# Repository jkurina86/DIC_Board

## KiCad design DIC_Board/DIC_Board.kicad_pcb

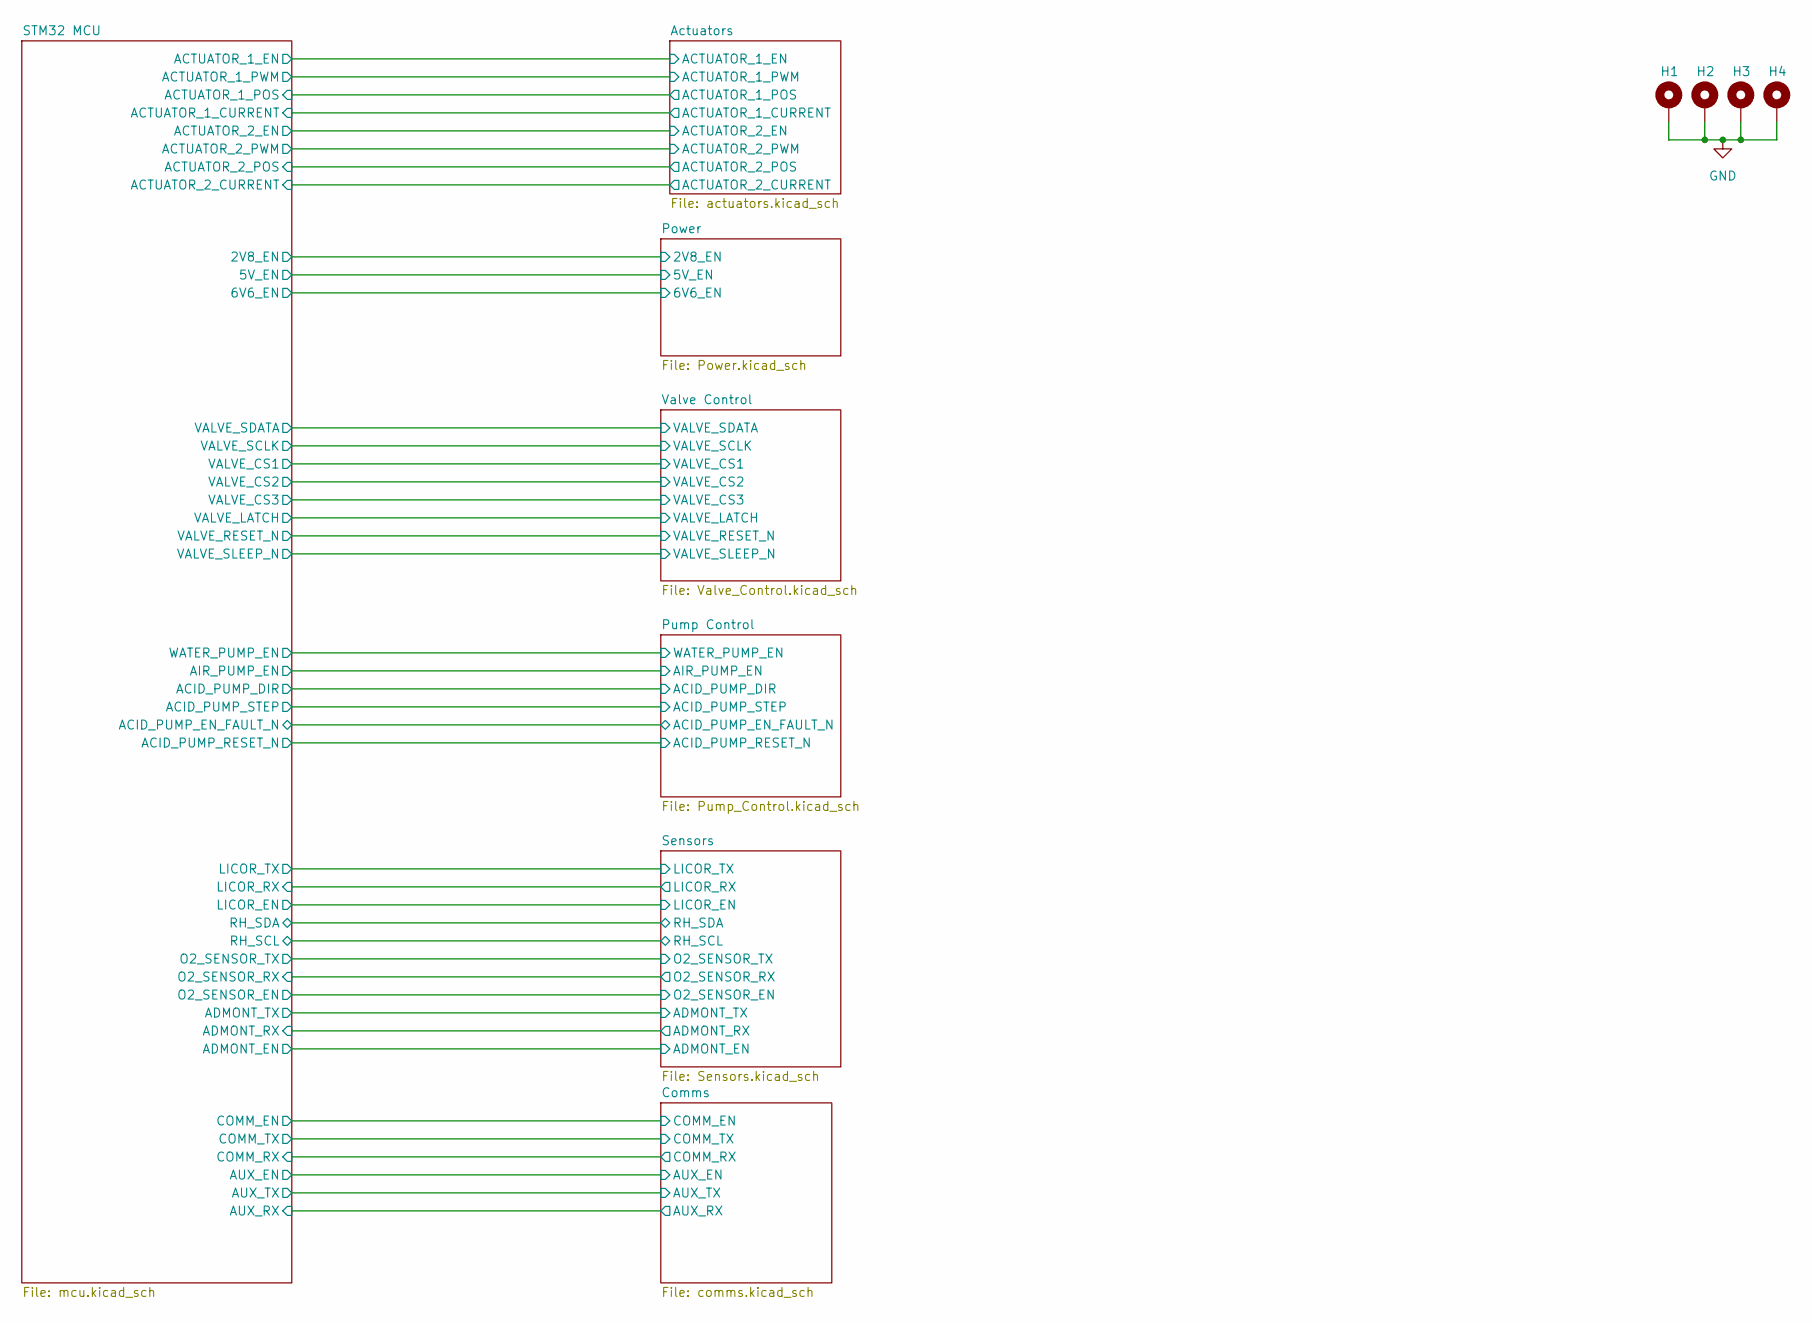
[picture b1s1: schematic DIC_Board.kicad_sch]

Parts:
H1, H2, H3, H4: MountingHole_2.5mm_Pad

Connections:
GND: H1.1 (1_1), H2.1 (1_1), H3.1 (1_1), H4.1 (1_1); also elsewhere on the board

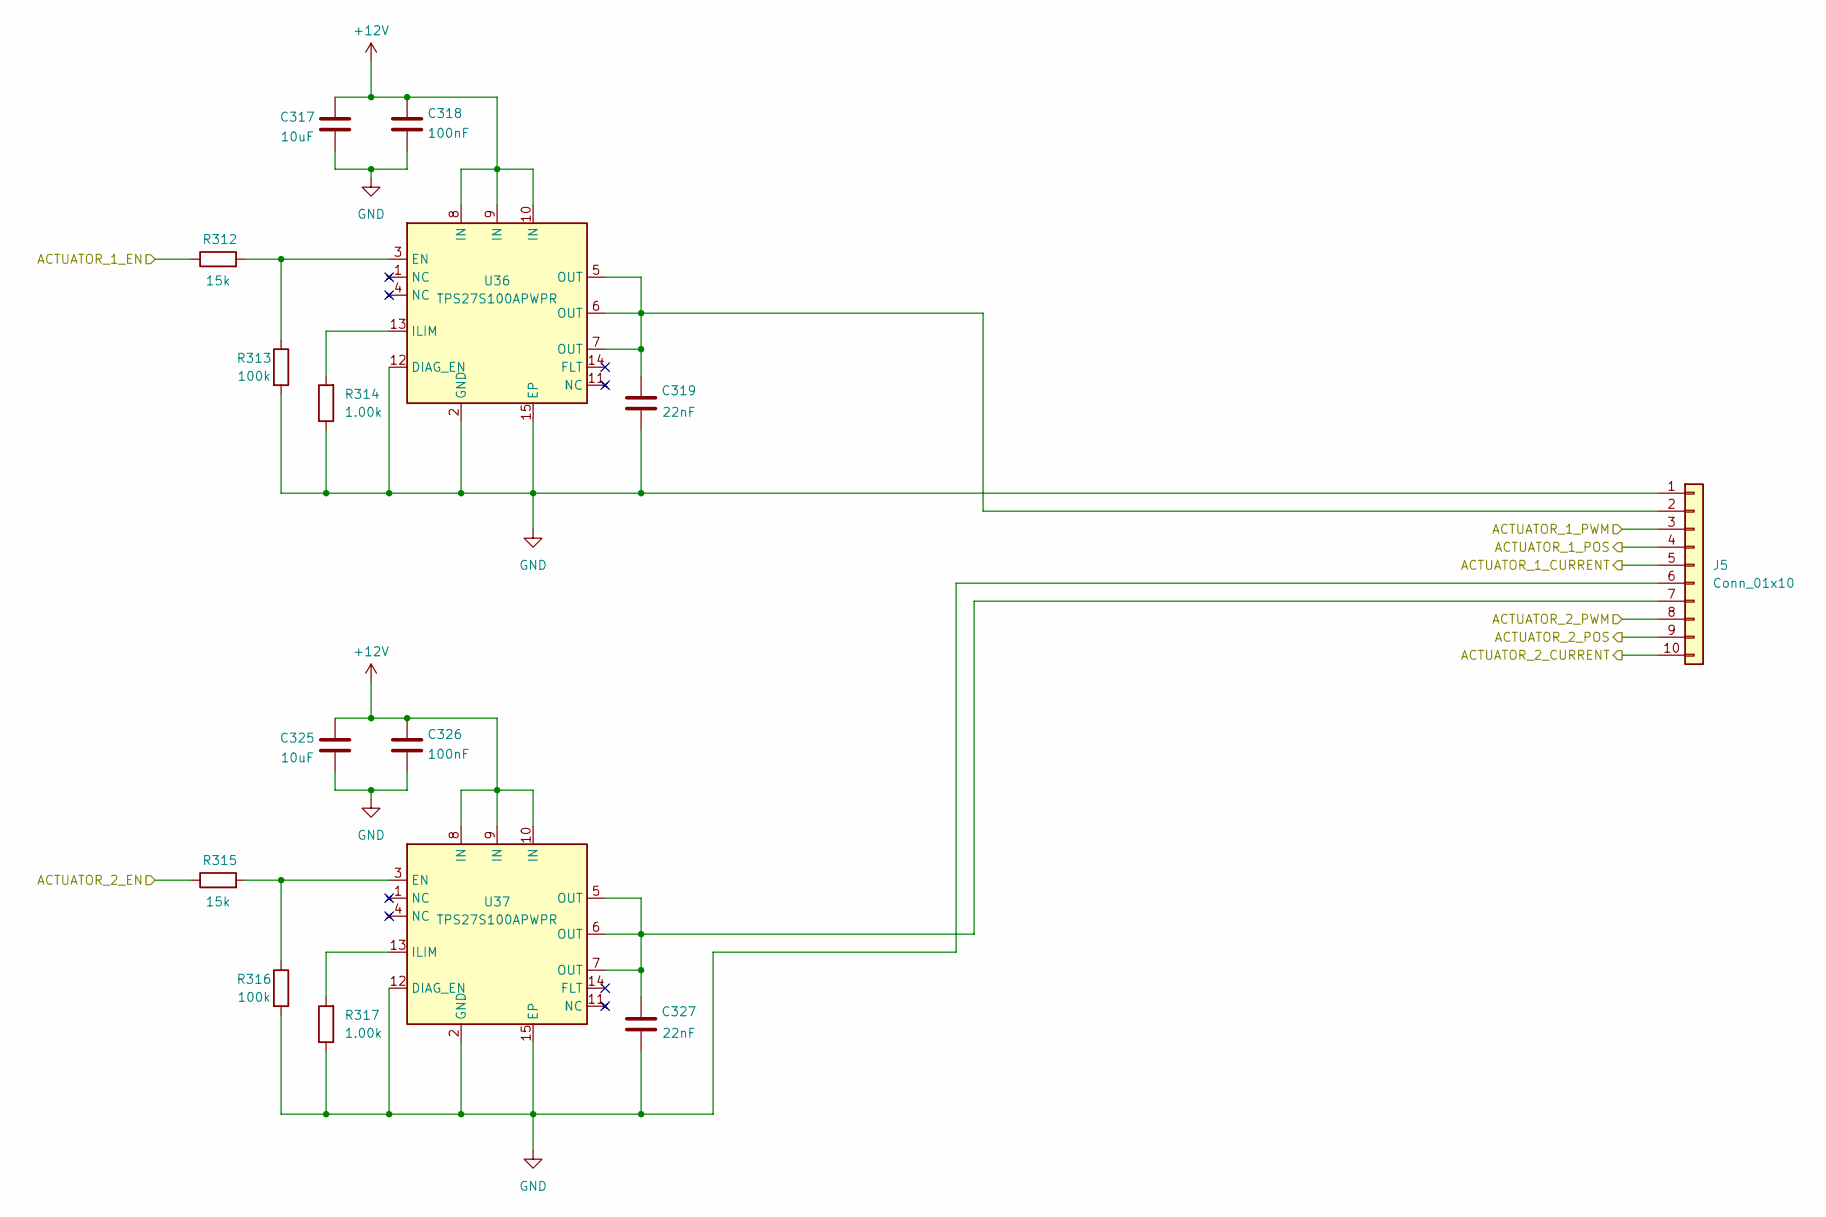
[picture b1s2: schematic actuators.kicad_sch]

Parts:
C317, C325: 10uF; C_1206_3216Metric; MPN CGA5L1X7R1H106K160AC
C318, C326: 100nF; C_0402_1005Metric; MPN GRM155R71H104ME14D
C319, C327: 22nF; C_0402_1005Metric; MPN GRM155R71H223KA12D
J5: Conn_01x10; Molex_Micro-Fit_3.0_43045-1000_2x05_P3.00mm_Horizontal; MPN 0430451000
R312, R315: 15k; R_0402_1005Metric; MPN CRCW040215K0FKED
R313, R316: 100k; R_0402_1005Metric; MPN CRCW0402100KFKED
R314, R317: 1.00k; R_0402_1005Metric; MPN CRCW04021K00FKED
U36, U37: TPS27S100APWPR; TPS27S100_Thermal_Drill0p3; MPN TPS27S100APWPR; DigiKey 296-49002-1-ND

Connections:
+12V: C317.1, C318.1, C325.1, C326.1, U36.8 (IN), U36.9 (IN), U36.10 (IN), U37.8 (IN), U37.9 (IN), U37.10 (IN); also elsewhere on the board
/Actuators/ACTUATOR_1_CURRENT: J5.5; also elsewhere on the board
/Actuators/ACTUATOR_1_EN: R312.1; also elsewhere on the board
/Actuators/ACTUATOR_1_POS: J5.4; also elsewhere on the board
/Actuators/ACTUATOR_1_PWM: J5.3; also elsewhere on the board
/Actuators/ACTUATOR_2_CURRENT: J5.10; also elsewhere on the board
/Actuators/ACTUATOR_2_EN: R315.1; also elsewhere on the board
/Actuators/ACTUATOR_2_POS: J5.9; also elsewhere on the board
/Actuators/ACTUATOR_2_PWM: J5.8; also elsewhere on the board
GND: C317.2, C318.2, C319.2, C325.2, C326.2, C327.2, J5.1, J5.6, R313.2, R314.1, R316.2, R317.1, U36.2 (GND), U36.12 (DIAG_EN), U36.15 (EP), U37.2 (GND), U37.12 (DIAG_EN), U37.15 (EP); also elsewhere on the board
unnamed: C319.1, J5.2, U36.5 (OUT), U36.6 (OUT), U36.7 (OUT)
unnamed: C327.1, J5.7, U37.5 (OUT), U37.6 (OUT), U37.7 (OUT)
unnamed: R312.2, R313.1, U36.3 (EN)
unnamed: R314.2, U36.13 (ILIM)
unnamed: R315.2, R316.1, U37.3 (EN)
unnamed: R317.2, U37.13 (ILIM)

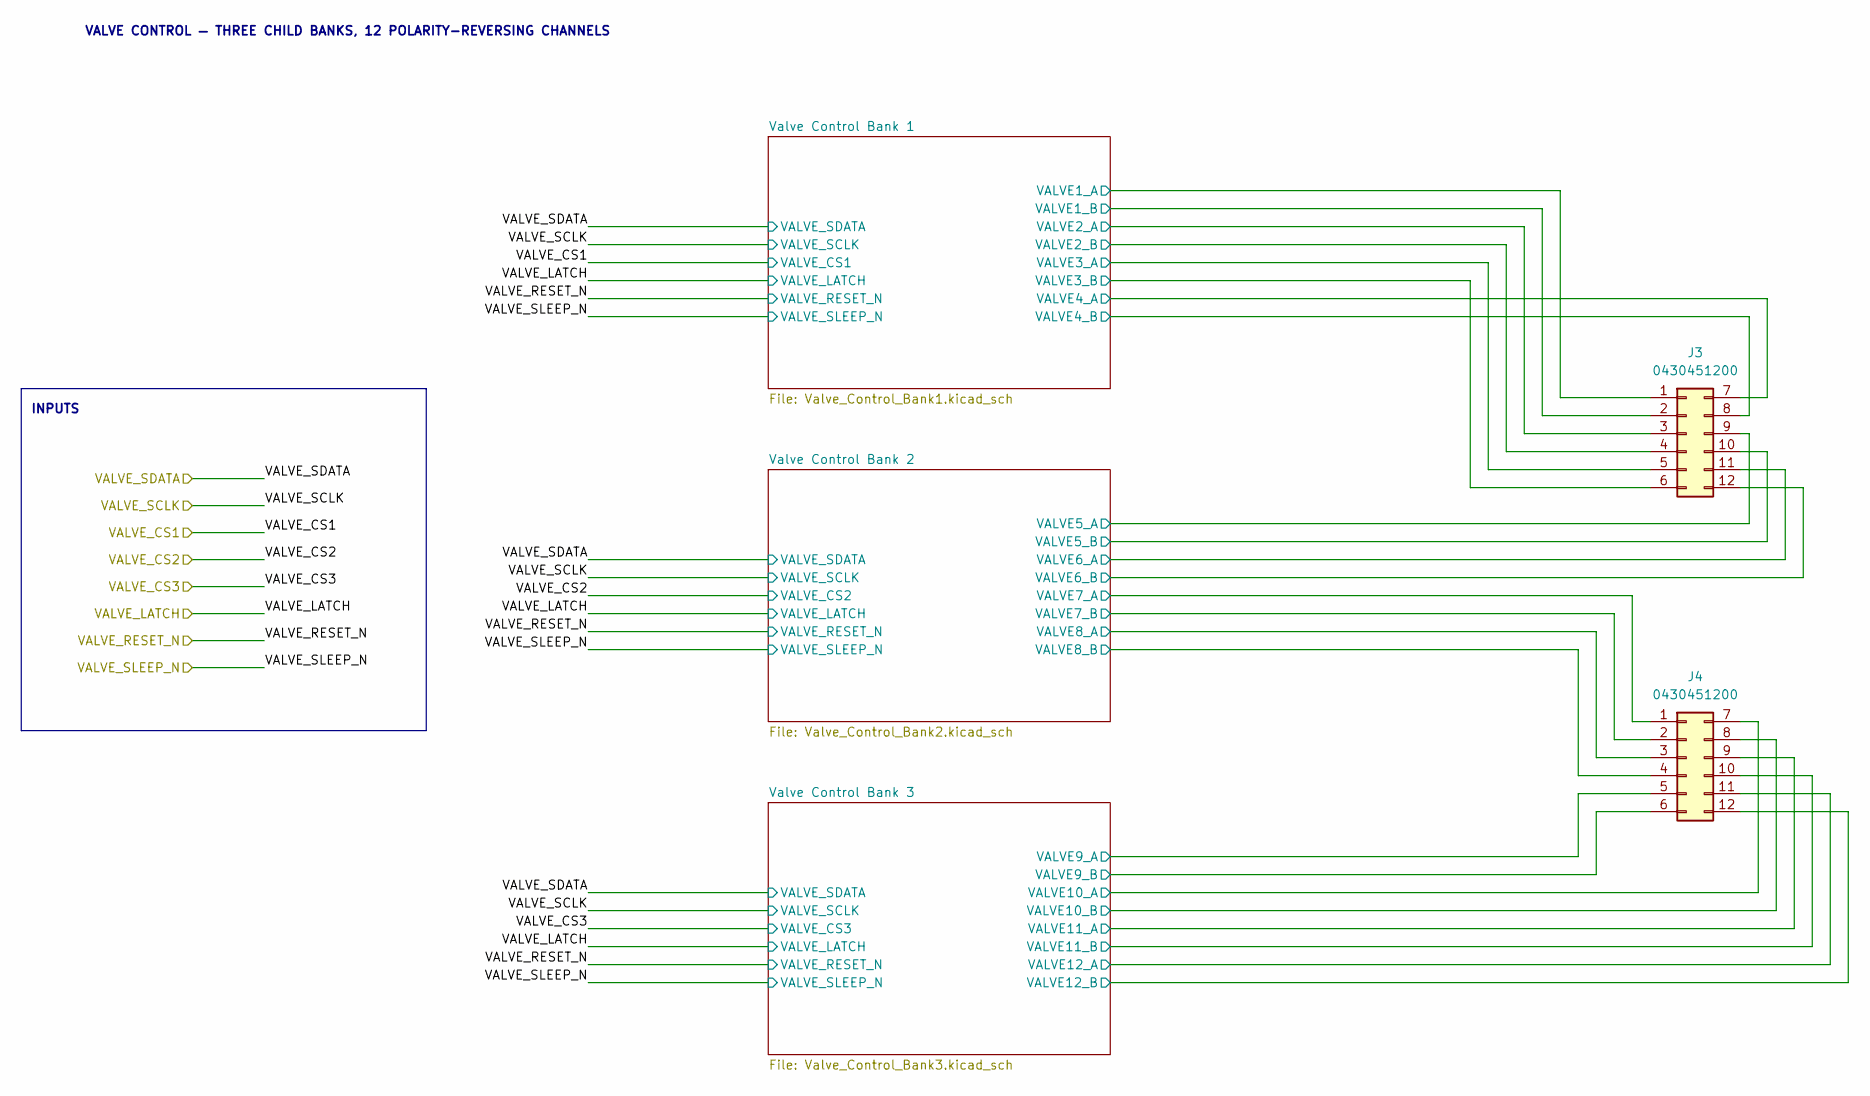
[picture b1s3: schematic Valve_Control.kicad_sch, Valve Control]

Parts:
J3, J4: 0430451200; Molex_Micro-Fit_3.0_43045-1200_2x06_P3.00mm_Horizontal; MPN 0430451200; DigiKey WM1818-ND

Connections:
/Valve Control/Valve Control Bank 1/VALVE1_A: J3.1; also elsewhere on the board
/Valve Control/Valve Control Bank 1/VALVE1_B: J3.2; also elsewhere on the board
/Valve Control/Valve Control Bank 1/VALVE2_A: J3.3; also elsewhere on the board
/Valve Control/Valve Control Bank 1/VALVE2_B: J3.4; also elsewhere on the board
/Valve Control/Valve Control Bank 1/VALVE3_A: J3.5; also elsewhere on the board
/Valve Control/Valve Control Bank 1/VALVE3_B: J3.6; also elsewhere on the board
/Valve Control/Valve Control Bank 1/VALVE4_A: J3.7; also elsewhere on the board
/Valve Control/Valve Control Bank 1/VALVE4_B: J3.8; also elsewhere on the board
/Valve Control/Valve Control Bank 2/VALVE5_A: J3.9; also elsewhere on the board
/Valve Control/Valve Control Bank 2/VALVE5_B: J3.10; also elsewhere on the board
/Valve Control/Valve Control Bank 2/VALVE6_A: J3.11; also elsewhere on the board
/Valve Control/Valve Control Bank 2/VALVE6_B: J3.12; also elsewhere on the board
/Valve Control/Valve Control Bank 2/VALVE7_A: J4.1; also elsewhere on the board
/Valve Control/Valve Control Bank 2/VALVE7_B: J4.2; also elsewhere on the board
/Valve Control/Valve Control Bank 2/VALVE8_A: J4.3; also elsewhere on the board
/Valve Control/Valve Control Bank 2/VALVE8_B: J4.4; also elsewhere on the board
/Valve Control/Valve Control Bank 3/VALVE9_A: J4.5; also elsewhere on the board
/Valve Control/Valve Control Bank 3/VALVE9_B: J4.6; also elsewhere on the board
/Valve Control/Valve Control Bank 3/VALVE10_A: J4.7; also elsewhere on the board
/Valve Control/Valve Control Bank 3/VALVE10_B: J4.8; also elsewhere on the board
/Valve Control/Valve Control Bank 3/VALVE11_A: J4.9; also elsewhere on the board
/Valve Control/Valve Control Bank 3/VALVE11_B: J4.10; also elsewhere on the board
/Valve Control/Valve Control Bank 3/VALVE12_A: J4.11; also elsewhere on the board
/Valve Control/Valve Control Bank 3/VALVE12_B: J4.12; also elsewhere on the board

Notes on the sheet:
INPUTS
VALVE CONTROL — THREE CHILD BANKS, 12 POLARITY-REVERSING CHANNELS

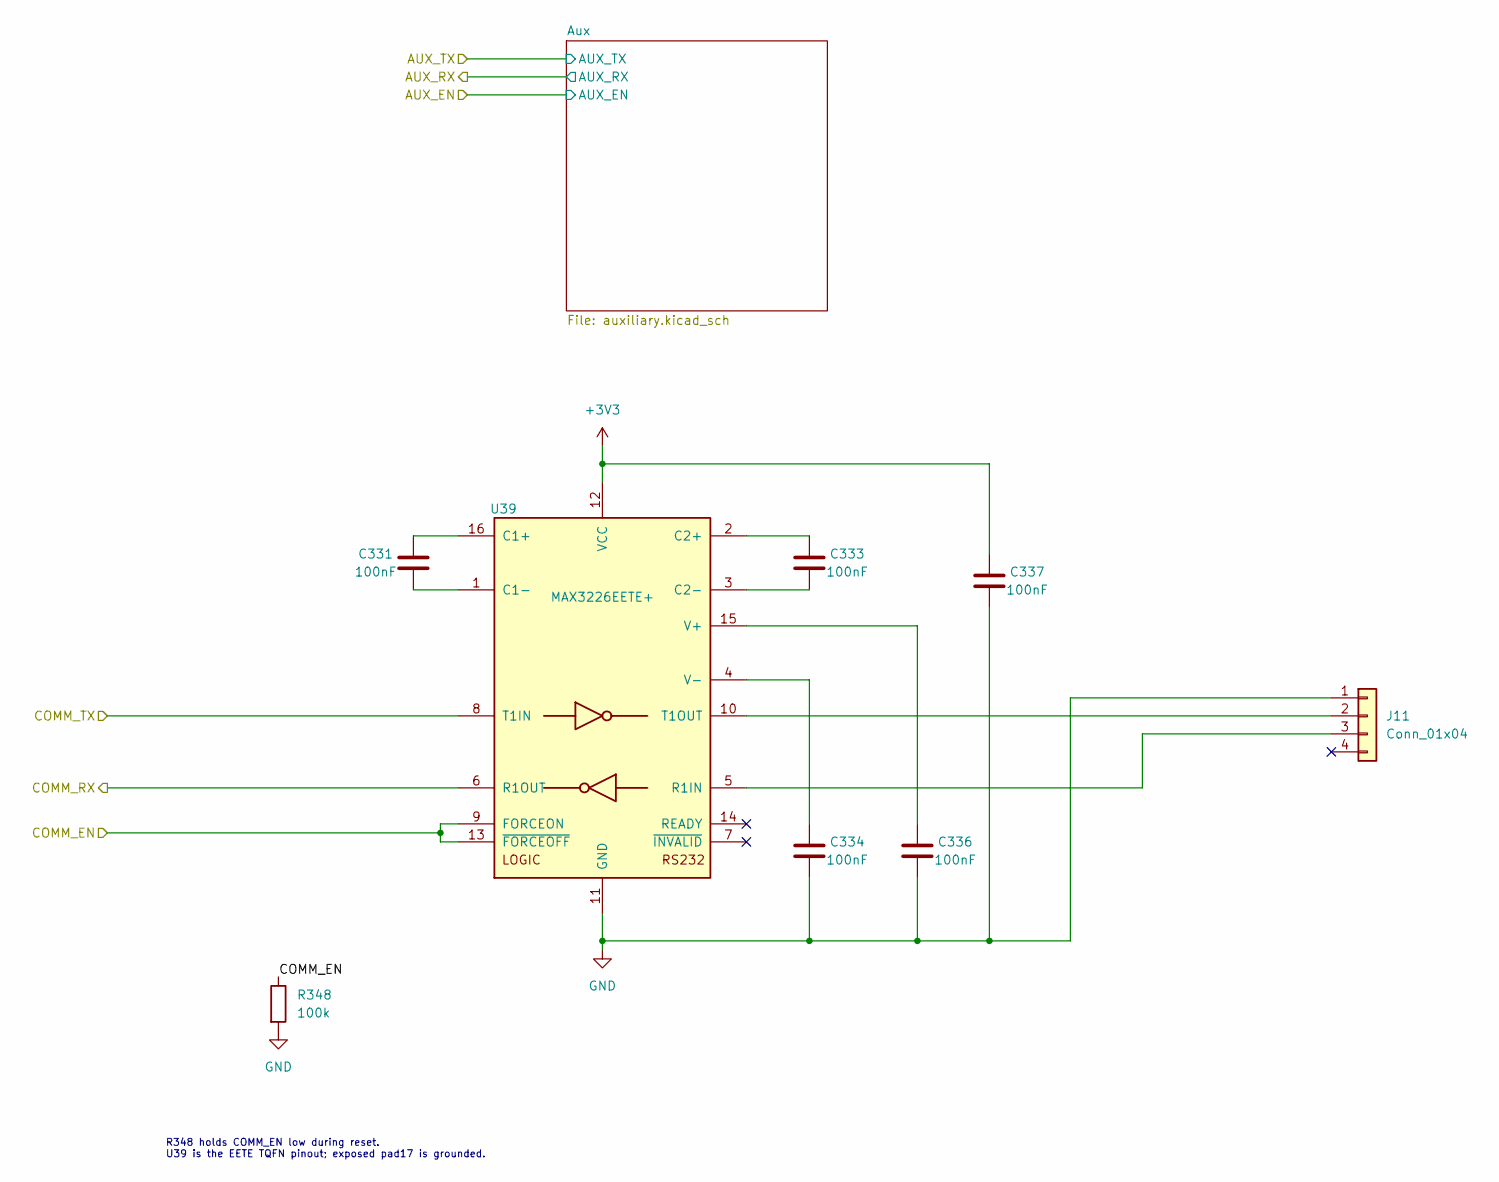
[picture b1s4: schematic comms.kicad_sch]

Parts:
C331, C333, C334, C336, C337: 100nF; C_0402_1005Metric; MPN GRM155R71H104ME14D
J11: Conn_01x04; Molex_Micro-Fit_3.0_43045-0400_2x02_P3.00mm_Horizontal; MPN 0430450400
R348: 100k; R_0603_1608Metric; Tolerance 1%; Power Rating 0.125W; MPN CRCW0603100KFKEA
U39: MAX3226EETE+; TQFN-16-1EP_5x5mm_P0.8mm_EP3.1x3.1mm; MPN MAX3226EETE+

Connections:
+3V3: C337.1, U39.12 (VCC); also elsewhere on the board
/Comms/COMM_EN: R348.1, U39.9 (FORCEON), U39.13 (~FORCEOFF); also elsewhere on the board
/Comms/COMM_RX: U39.6 (R1OUT); also elsewhere on the board
/Comms/COMM_TX: U39.8 (T1IN); also elsewhere on the board
GND: C334.2, C336.2, C337.2, J11.1, R348.2, U39.11 (GND), U39.17 (EP); also elsewhere on the board
unnamed: J11.2, U39.10 (T1OUT)
unnamed: J11.3, U39.5 (R1IN)
unnamed: C331.1, U39.16 (C1+)
unnamed: C331.2, U39.1 (C1-)
unnamed: C333.1, U39.2 (C2+)
unnamed: C333.2, U39.3 (C2-)
unnamed: C336.1, U39.15 (V+)
unnamed: C334.1, U39.4 (V-)

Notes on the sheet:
R348 holds COMM_EN low during reset. U39 is the EETE TQFN pinout; exposed pad17 is grounded.

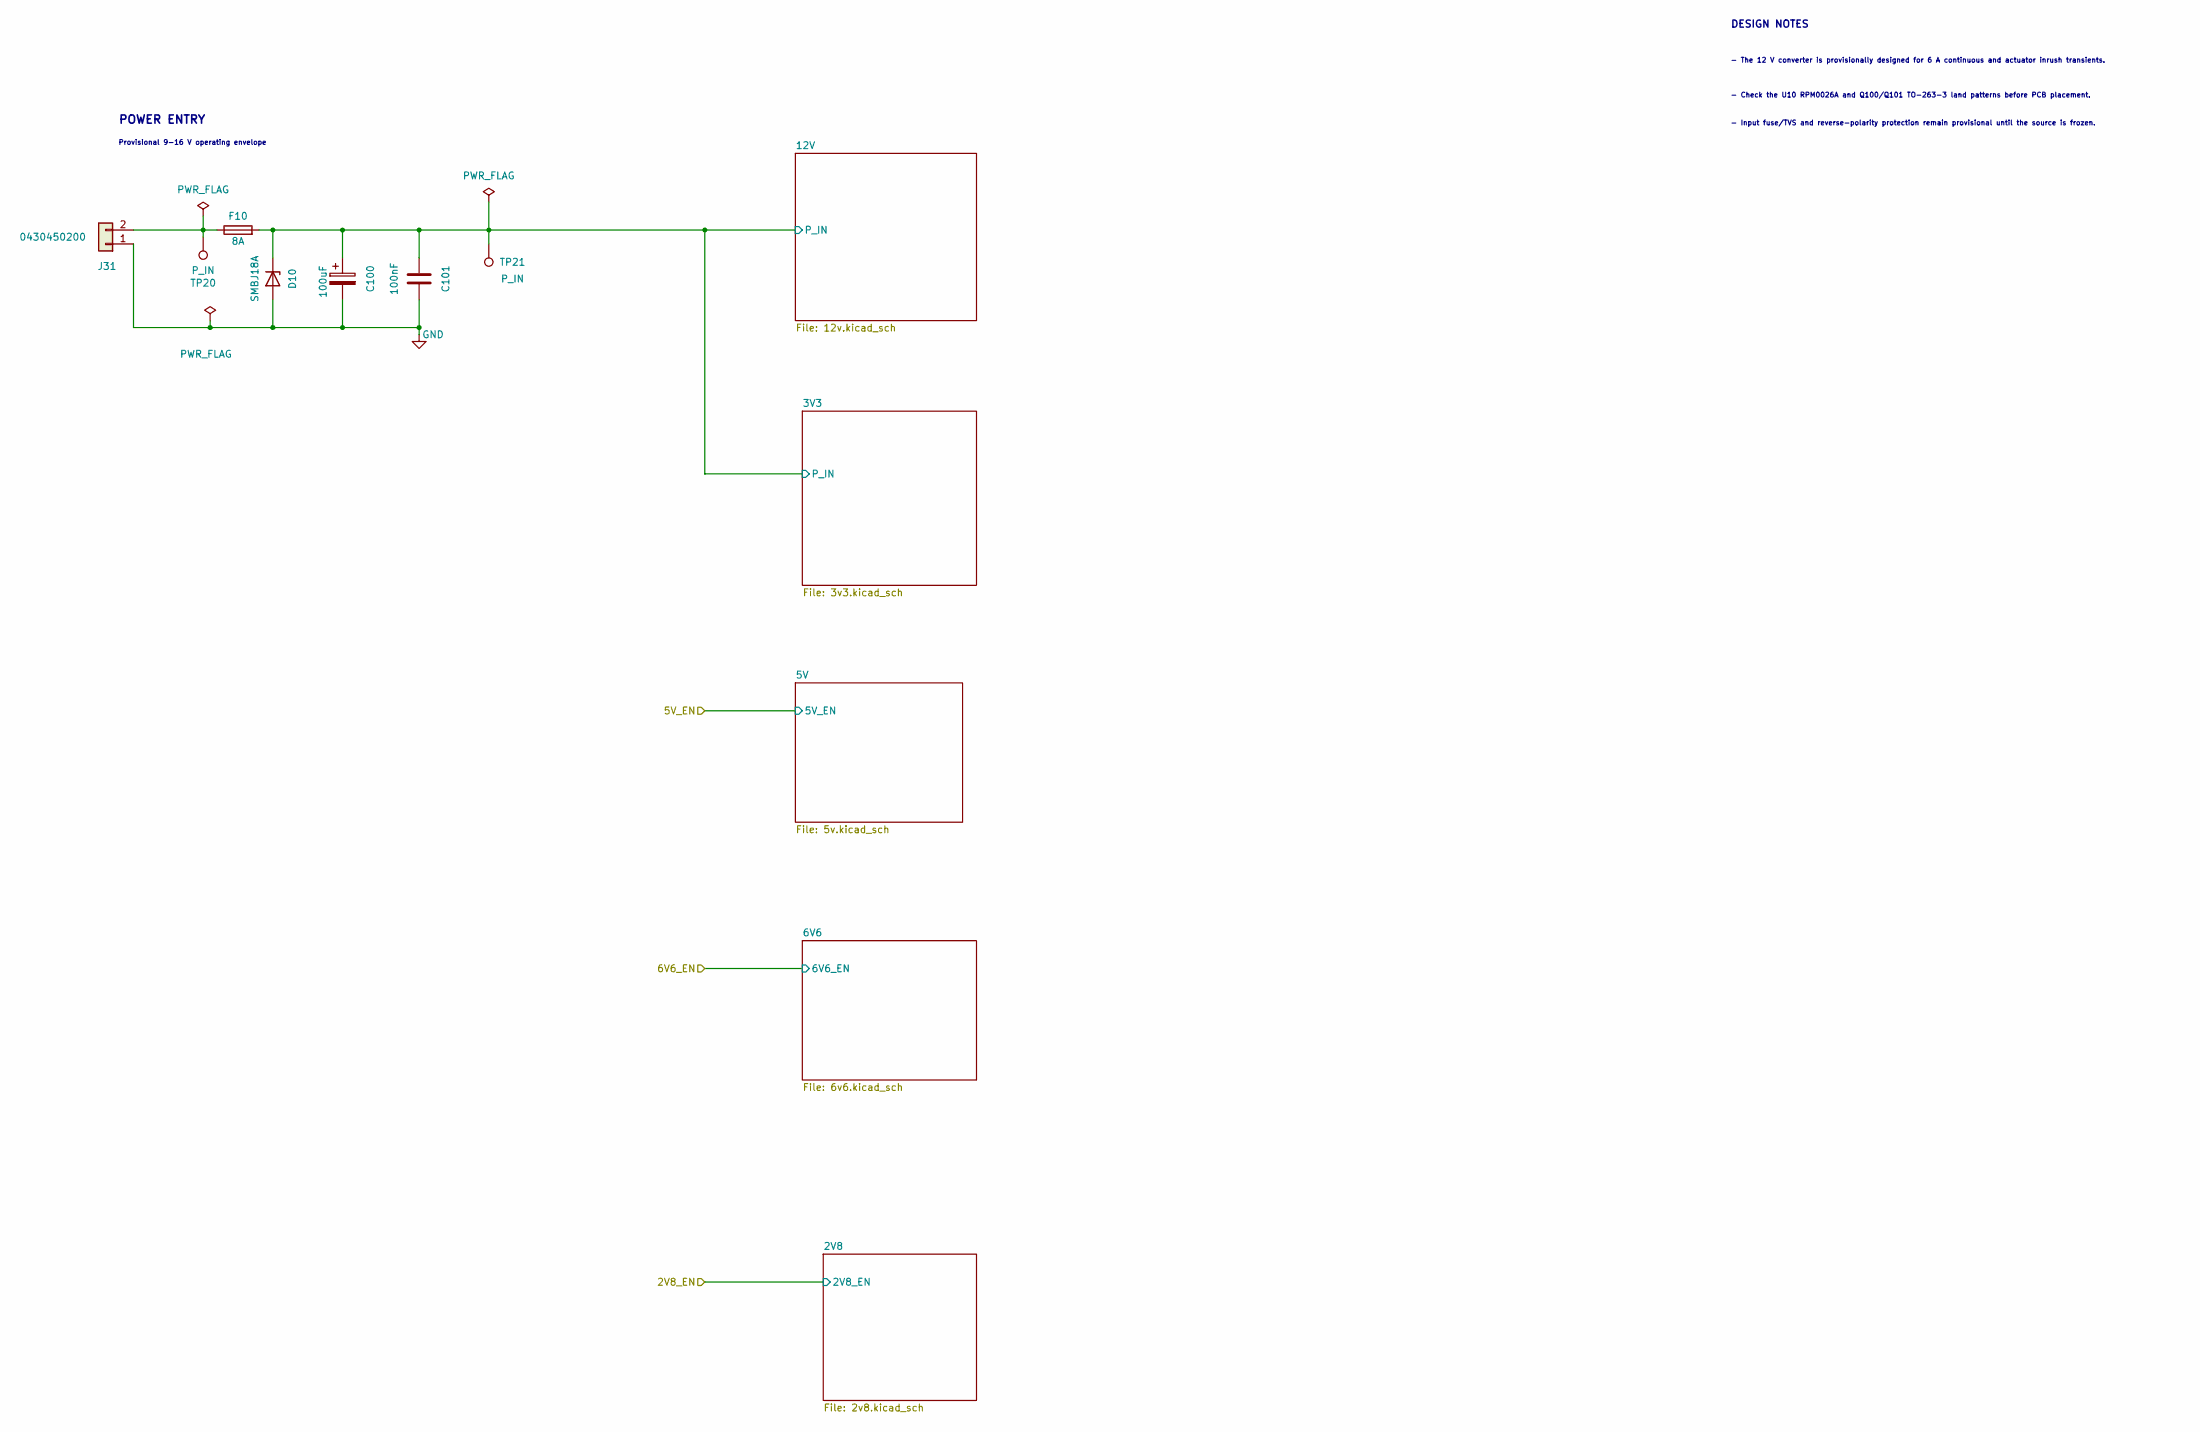
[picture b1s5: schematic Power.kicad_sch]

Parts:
C100: 100uF; CP_Elec_8x10.5; MPN EEHZA1V101P
C101: 100nF; C_0402_1005Metric; MPN GRM155R71H104ME14D
D10: SMBJ18A; D_SMB; MPN SMBJ18A
F10: 8A; Fuse_Littelfuse-NANO2-451_453; Current Rating 8A; Voltage Rating 125VAC / 125VDC; MPN 0451008.MRL
J31: 0430450200; Molex_Micro-Fit_3.0_43045-0200_2x01_P3.00mm_Horizontal; MPN 0430450200; DigiKey WM1813-ND
TP20, TP21: P_IN; TestPoint_Pad_D1.0mm

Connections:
/Power/12V/P_IN: C100.1, C101.1, D10.1 (K), F10.2, TP21.1 (1_1); also elsewhere on the board
GND: C100.2, C101.2, D10.2 (A), J31.1; also elsewhere on the board
unnamed: F10.1, J31.2, TP20.1 (1_1)

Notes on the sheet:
- Check the U10 RPM0026A and Q100/Q101 TO-263-3 land patterns before PCB placement.
- Input fuse/TVS and reverse-polarity protection remain provisional until the source is frozen.
- The 12 V converter is provisionally designed for 6 A continuous and actuator inrush transients.
DESIGN NOTES
Provisional 9-16 V operating envelope
POWER ENTRY

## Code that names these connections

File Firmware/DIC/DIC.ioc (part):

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Mcu.Name=STM32L476Z(E-G)Tx
Mcu.Package=LQFP144
Mcu.UserName=STM32L476ZGTx
PA0.GPIOParameters=GPIO_Label
PA0.GPIO_Label=ADMONT_TX
PA0.Mode=Asynchronous
PA0.Signal=UART4_TX
PA1.GPIOParameters=GPIO_Label
PA1.GPIO_Label=ADMONT_RX
PA1.Mode=Asynchronous
PA1.Signal=UART4_RX
PA10.Mode=Asynchronous
PA10.GPIOParameters=GPIO_Label
PA10.GPIO_Label=COMM_RX
PA10.Signal=USART1_RX
PA11.Mode=Device_Only
PA11.Signal=USB_OTG_FS_DM
PA12.Mode=Device_Only
PA12.Signal=USB_OTG_FS_DP
PA13\ (JTMS-SWDIO).Mode=Serial_Wire
PA13\ (JTMS-SWDIO).Signal=SYS_JTMS-SWDIO
PA14\ (JTCK-SWCLK).Mode=Serial_Wire
PA14\ (JTCK-SWCLK).Signal=SYS_JTCK-SWCLK
PA2.GPIOParameters=GPIO_Label
PA2.GPIO_Label=LICOR_TX
PA2.Mode=Asynchronous
PA2.Signal=USART2_TX
PA3.GPIOParameters=GPIO_Label
PA3.GPIO_Label=LICOR_RX
PA3.Mode=Asynchronous
PA3.Signal=USART2_RX
PA4.GPIOParameters=GPIO_Label
PA4.GPIO_Label=RTC_CE
PA4.Signal=GPIO_Output
PA5.Mode=Full_Duplex_Master
PA5.Signal=SPI1_SCK
PA6.Mode=Full_Duplex_Master
PA6.Signal=SPI1_MISO
PA7.Mode=Full_Duplex_Master
PA7.Signal=SPI1_MOSI
PA8.GPIOParameters=GPIO_Label,PinState
PA8.GPIO_Label=COMM_EN
PA8.PinState=GPIO_PIN_RESET
PA8.Signal=GPIO_Output
PA9.GPIOParameters=GPIO_Label
PA9.GPIO_Label=COMM_TX
PA9.Mode=Asynchronous
PA9.Signal=USART1_TX
PC13.Signal=GPIO_Input
PB0.GPIOParameters=GPIO_Label
PB0.GPIO_Label=RTC_INT
PB0.Signal=GPIO_Input
PB1.GPIOParameters=GPIO_Label
PB1.GPIO_Label=RTC_CLKOUT
PB1.Signal=GPIO_Input
PB10.GPIOParameters=GPIO_Label
PB10.GPIO_Label=VALVE_CS1
PB10.Signal=GPIO_Output
PB11.GPIOParameters=GPIO_Label
PB11.GPIO_Label=VALVE_CS2
PB11.Signal=GPIO_Output
PB12.GPIOParameters=GPIO_Label
PB12.GPIO_Label=VALVE_CS3
PB12.Signal=GPIO_Output
PB13.GPIOParameters=GPIO_Label
PB13.GPIO_Label=VALVE_LATCH
PB13.Signal=GPIO_Output
PB14.GPIOParameters=GPIO_Label
PB14.GPIO_Label=VALVE_RESET_N
PB14.Signal=GPIO_Output
PB15.GPIOParameters=GPIO_Label
PB15.GPIO_Label=VALVE_SLEEP_N
PB15.Signal=GPIO_Output
PB2.GPIOParameters=GPIO_Label
PB2.GPIO_Label=RTC_CLKOE
PB2.Signal=GPIO_Output
PE12.Mode=Single Bank
PE12.Signal=QUADSPI_BK1_IO0
PB3\ (JTDO-TRACESWO).Signal=SYS_JTDO-SWO
PC0.GPIOParameters=GPIO_Label
PC0.GPIO_Label=ACTUATOR_1_POS
PC0.Signal=ADCx_IN1
PC1.GPIOParameters=GPIO_Label
PC1.GPIO_Label=ACTUATOR_1_CURRENT
PC1.Signal=ADCx_IN2
PC10.Mode=SD_4_bits_Wide_bus
PC10.Signal=SDMMC1_D2
PC11.Mode=SD_4_bits_Wide_bus
PC11.Signal=SDMMC1_D3
PC12.Mode=SD_4_bits_Wide_bus
PC12.Signal=SDMMC1_CK
PC14-OSC32_IN\ (PC14).Mode=LSE-External-Oscillator
PC14-OSC32_IN\ (PC14).Signal=RCC_OSC32_IN
PC15-OSC32_OUT\ (PC15).Mode=LSE-External-Oscillator
PC15-OSC32_OUT\ (PC15).Signal=RCC_OSC32_OUT
PC2.GPIOParameters=GPIO_Label
PC2.GPIO_Label=ACTUATOR_2_POS
PC2.Signal=ADCx_IN3
PC3.GPIOParameters=GPIO_Label
PC3.GPIO_Label=ACTUATOR_2_CURRENT
PC3.Signal=ADCx_IN4
PC4.GPIOParameters=GPIO_Label
PC4.GPIO_Label=O2_SENSOR_TX
PC4.Mode=Asynchronous
PC4.Signal=USART3_TX
PC5.GPIOParameters=GPIO_Label
PC5.GPIO_Label=O2_SENSOR_RX
PC5.Mode=Asynchronous
PC5.Signal=USART3_RX
PC8.Mode=SD_4_bits_Wide_bus
PC8.Signal=SDMMC1_D0
PC9.Mode=SD_4_bits_Wide_bus
PC9.Signal=SDMMC1_D1
PD12.GPIOParameters=GPIO_Label
PD12.GPIO_Label=ACID_PUMP_STEP
PD12.Signal=S_TIM4_CH1
PD2.Mode=SD_4_bits_Wide_bus
PD2.Signal=SDMMC1_CMD
PE10.Mode=Single Bank
PE10.Signal=QUADSPI_CLK
PE11.Mode=Single Bank
PE11.Signal=QUADSPI_NCS
PE13.Mode=Single Bank
PE13.Signal=QUADSPI_BK1_IO1
PE14.Mode=Single Bank
PE14.Signal=QUADSPI_BK1_IO2
PE15.Mode=Single Bank
PE15.Signal=QUADSPI_BK1_IO3
PE0.GPIOParameters=GPIO_Label
PE0.GPIO_Label=USB_VBUS_SENSE
PE0.Signal=GPIO_Input
PF0.GPIOParameters=GPIO_Label,PinState
PF0.GPIO_Label=EN_2V8
PF0.PinState=GPIO_PIN_SET
PF0.Signal=GPIO_Output
PF1.GPIOParameters=GPIO_Label,PinState
PF1.GPIO_Label=EN_5V
PF1.PinState=GPIO_PIN_SET
PF1.Signal=GPIO_Output
PF10.GPIOParameters=GPIO_Label
PF10.GPIO_Label=AIR_PUMP_EN
PF10.Signal=GPIO_Output
PF11.GPIOParameters=GPIO_Label,PinState
PF11.GPIO_Label=ACID_PUMP_DIR
PF11.PinState=GPIO_PIN_SET
PF11.Signal=GPIO_Output
PF12.GPIOParameters=GPIO_Label,GPIO_ModeDefaultOutputPP,PinState
PF12.GPIO_Label=ACID_PUMP_EN_FAULT_N
PF12.GPIO_ModeDefaultOutputPP=GPIO_MODE_OUTPUT_OD
PF12.PinState=GPIO_PIN_SET
PF12.Signal=GPIO_Output
PF13.GPIOParameters=GPIO_Label
PF13.GPIO_Label=ACID_PUMP_RESET_N
PF13.Signal=GPIO_Output
PF14.GPIOParameters=GPIO_Label
PF14.GPIO_Label=ACTUATOR_1_EN
PF14.Signal=GPIO_Output
PF15.GPIOParameters=GPIO_Label
PF15.GPIO_Label=ACTUATOR_2_EN
PF15.Signal=GPIO_Output
PF2.GPIOParameters=GPIO_Label,PinState
PF2.GPIO_Label=EN_6V6
PF2.PinState=GPIO_PIN_SET
PF2.Signal=GPIO_Output
PF3.GPIOParameters=GPIO_Label
PF3.GPIO_Label=LICOR_EN
PF3.Signal=GPIO_Output
PF4.GPIOParameters=GPIO_Label
PF4.GPIO_Label=O2_SENSOR_EN
PF4.Signal=GPIO_Output
PF5.GPIOParameters=GPIO_Label
PF5.GPIO_Label=ADMONT_EN
PF5.Signal=GPIO_Output
PF6.GPIOParameters=GPIO_Label
PF6.GPIO_Label=ACTUATOR_1_PWM
PF6.Signal=S_TIM5_CH1
PF7.GPIOParameters=GPIO_Label
PF7.GPIO_Label=ACTUATOR_2_PWM
PF7.Signal=S_TIM5_CH2
PF9.GPIOParameters=GPIO_Label
PF9.GPIO_Label=WATER_PUMP_EN
PF9.Signal=GPIO_Output
PG11.GPIOParameters=GPIO_Label
PG11.GPIO_Label=VALVE_SDATA
PG11.Mode=Simplex_Bidirectional_Master
PG11.Signal=SPI3_MOSI
PG13.GPIOParameters=GPIO_Label
PG13.GPIO_Label=RH_SDA
PG13.Mode=I2C
PG13.Signal=I2C1_SDA
PG14.GPIOParameters=GPIO_Label
PG14.GPIO_Label=RH_SCL
PG14.Mode=I2C
PG14.Signal=I2C1_SCL
PG6.GPIOParameters=GPIO_Label,PinState
PG6.GPIO_Label=AUX_EN
PG6.PinState=GPIO_PIN_RESET
PG6.Signal=GPIO_Output
PG7.GPIOParameters=GPIO_Label
PG7.GPIO_Label=AUX_TX
PG7.Mode=Asynchronous
PG7.Signal=LPUART1_TX
PG8.GPIOParameters=GPIO_Label
PG8.GPIO_Label=AUX_RX
PG8.Mode=Asynchronous
PG8.Signal=LPUART1_RX
PG9.GPIOParameters=GPIO_Label
PG9.GPIO_Label=VALVE_SCLK
PG9.Mode=Simplex_Bidirectional_Master
PG9.Signal=SPI3_SCK
PH0-OSC_IN\ (PH0).Mode=HSE-External-Oscillator
PH0-OSC_IN\ (PH0).Signal=RCC_OSC_IN
PH1-OSC_OUT\ (PH1).Mode=HSE-External-Oscillator
PH1-OSC_OUT\ (PH1).Signal=RCC_OSC_OUT
RCC.HSE_VALUE=8000000
board=custom
RCC.SYSCLKSource=RCC_SYSCLKSOURCE_PLLCLK
RCC.SYSCLKFreq_VALUE=16000000
